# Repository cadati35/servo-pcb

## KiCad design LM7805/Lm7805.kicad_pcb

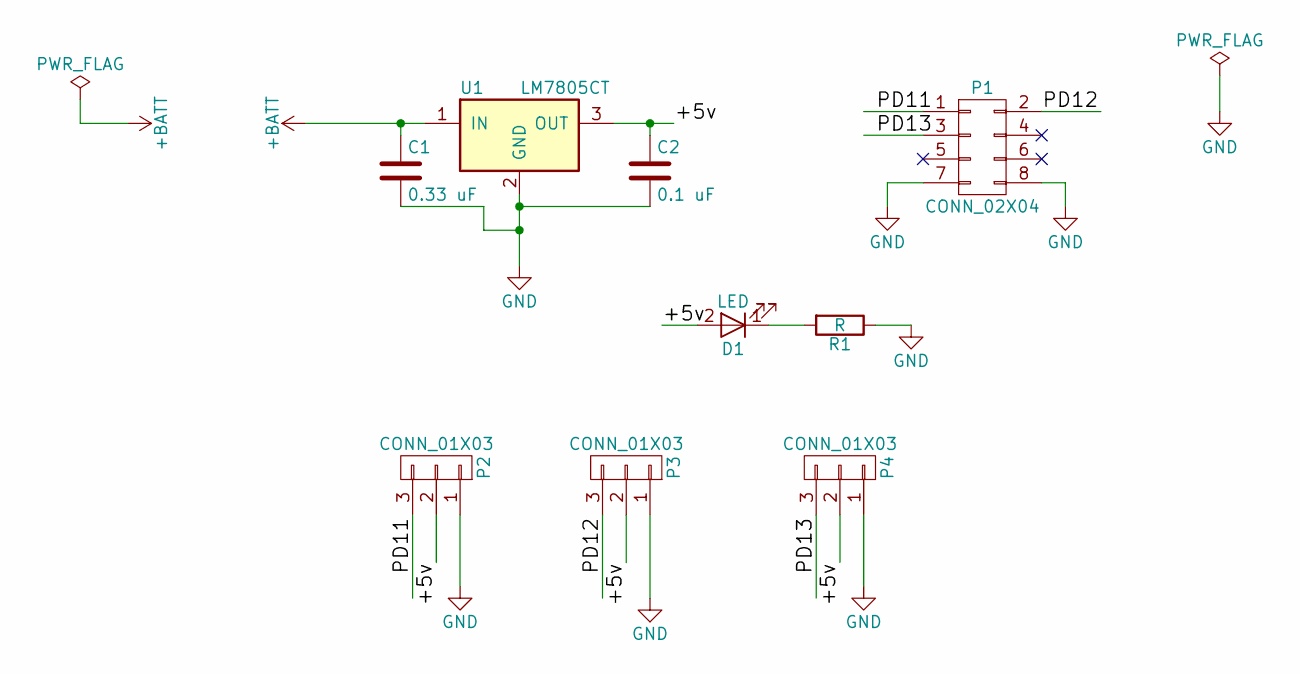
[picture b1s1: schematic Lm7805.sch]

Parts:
C1: 0.33 uF; C_Disc_D3.0mm_W1.6mm_P2.50mm
C2: 0.1 uF; C_Disc_D3.0mm_W1.6mm_P2.50mm
D1: LED; LED_D3.0mm
P1: CONN_02X04; IDC_Header_Straight_8pins
P2, P3, P4: CONN_01X03; Pin_Header_Angled_1x03_Pitch2.54mm
R1: R; R_Axial_DIN0204_L3.6mm_D1.6mm_P5.08mm_Horizontal
U1: LM7805CT; TO-220_Horizontal

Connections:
+BATT: C1.1, U1.1 (IN)
/+5v: C2.1, D1.2 (A), P2.2, P3.2, P4.2, U1.3 (OUT)
/PD11: P1.1, P2.3
/PD12: P1.2, P3.3
/PD13: P1.3, P4.3
GND: C1.2, C2.2, P1.7, P1.8, P2.1, P3.1, P4.1, R1.1, U1.2 (GND)
unnamed: D1.1 (K), R1.2

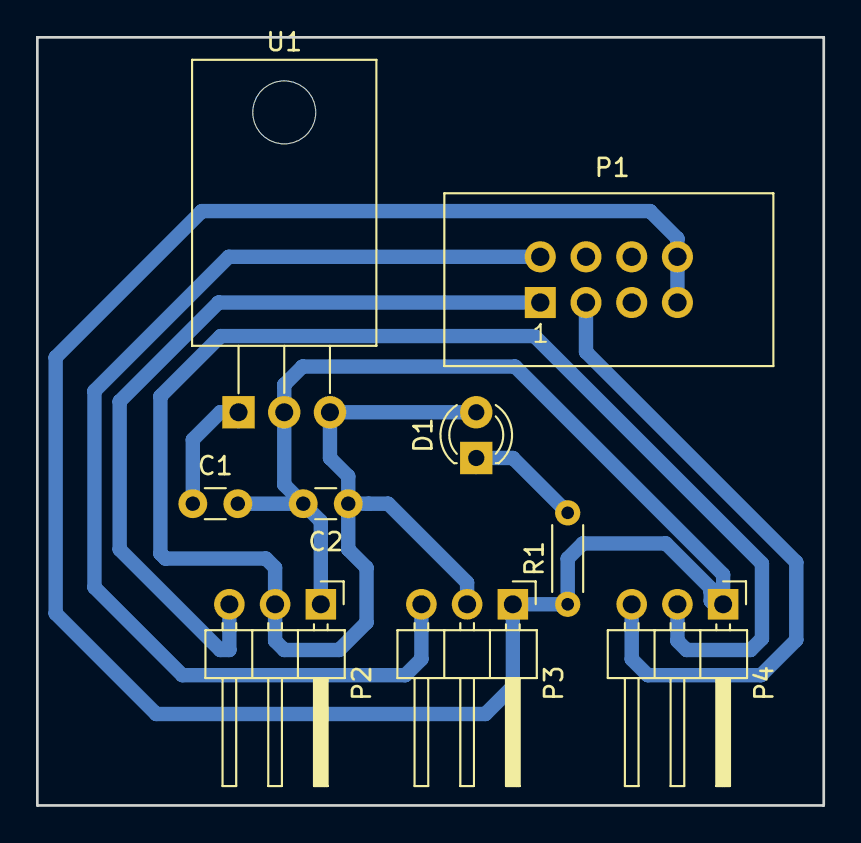
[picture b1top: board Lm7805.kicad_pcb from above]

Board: 2 copper layers, 43.7 x 42.7 mm, 9 parts (0 on the bottom side), 7 nets.

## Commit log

2017-08-24 working on schematic
2017-08-24 moved to LM7805 Folder
2017-08-25 avance pcb
2017-08-26 pcb lm7805 routeado
2017-08-29 final pcb
2017-08-29 Final pcb LM7805
